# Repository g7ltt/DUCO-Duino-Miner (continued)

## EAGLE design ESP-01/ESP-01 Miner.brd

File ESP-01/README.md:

# Duco Miner ESP-01 8DN
ESP-01 (ESP8266) based DUCO/Duino Coin miner. Uses up to 8 ESP-01 modules. WiFi/Network handled by the module itself.

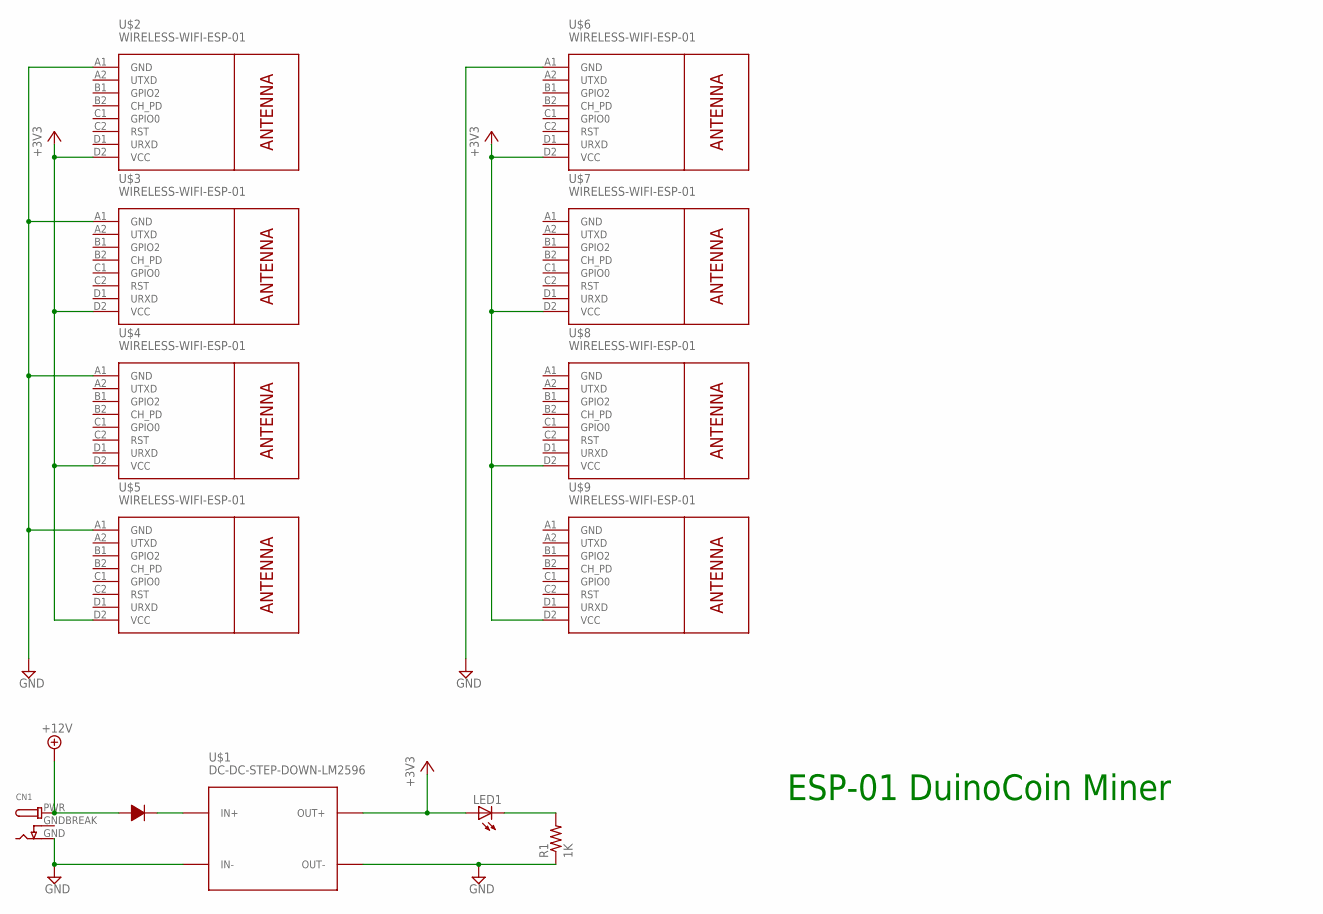
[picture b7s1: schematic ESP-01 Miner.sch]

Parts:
CN1: DCBARRELPTH; DCJACK_2MM_PTH
LED1: LED3MM
R1: 1K; 0204/7
U$1: DC-DC-STEP-DOWN-LM2596
U$2, U$3, U$4, U$5, U$6, U$7, U$8, U$9: WIRELESS-WIFI-ESP-01
U$10: 1N4001; DIODE-12.70

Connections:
+3V3: LED1.A, U$1.OUT+, U$2.D2 (VCC), U$3.D2 (VCC), U$4.D2 (VCC), U$5.D2 (VCC), U$6.D2 (VCC), U$7.D2 (VCC), U$8.D2 (VCC), U$9.D2 (VCC)
+12V: CN1.PWR, U$10.P$1
GND: CN1.GND, R1.1, U$1.IN-, U$1.OUT-, U$2.A1 (GND), U$3.A1 (GND), U$4.A1 (GND), U$5.A1 (GND), U$6.A1 (GND), U$7.A1 (GND), U$8.A1 (GND), U$9.A1 (GND)
GNDBREAK: CN1.GNDBREAK
unnamed: U$1.IN+, U$10.P$2
unnamed: LED1.K (C), R1.2

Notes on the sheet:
ESP-01 DuinoCoin Miner

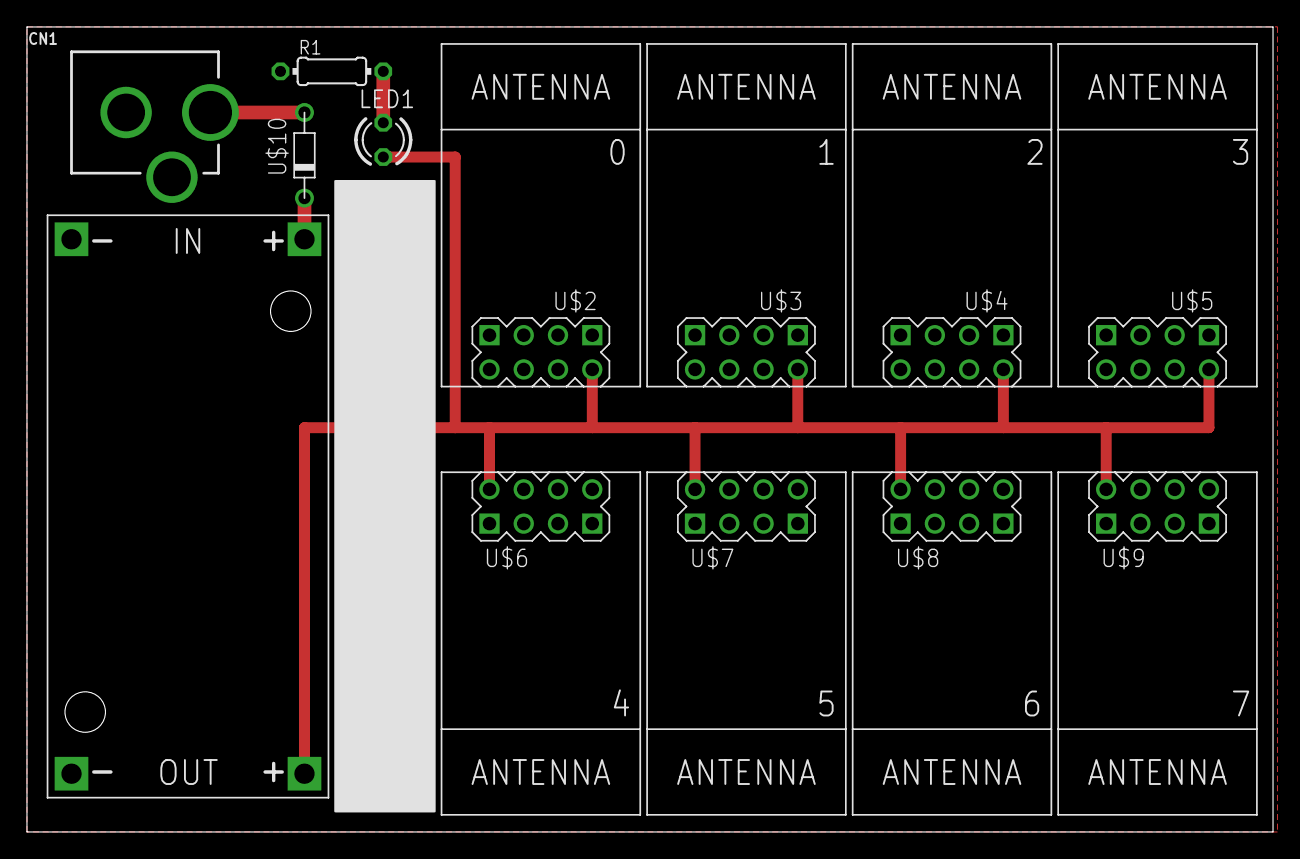
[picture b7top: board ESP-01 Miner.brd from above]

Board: 2 copper layers, 92.4 x 59.7 mm, 13 parts (0 on the bottom side), 5 nets.

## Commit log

2022-12-19 ESP-01/
